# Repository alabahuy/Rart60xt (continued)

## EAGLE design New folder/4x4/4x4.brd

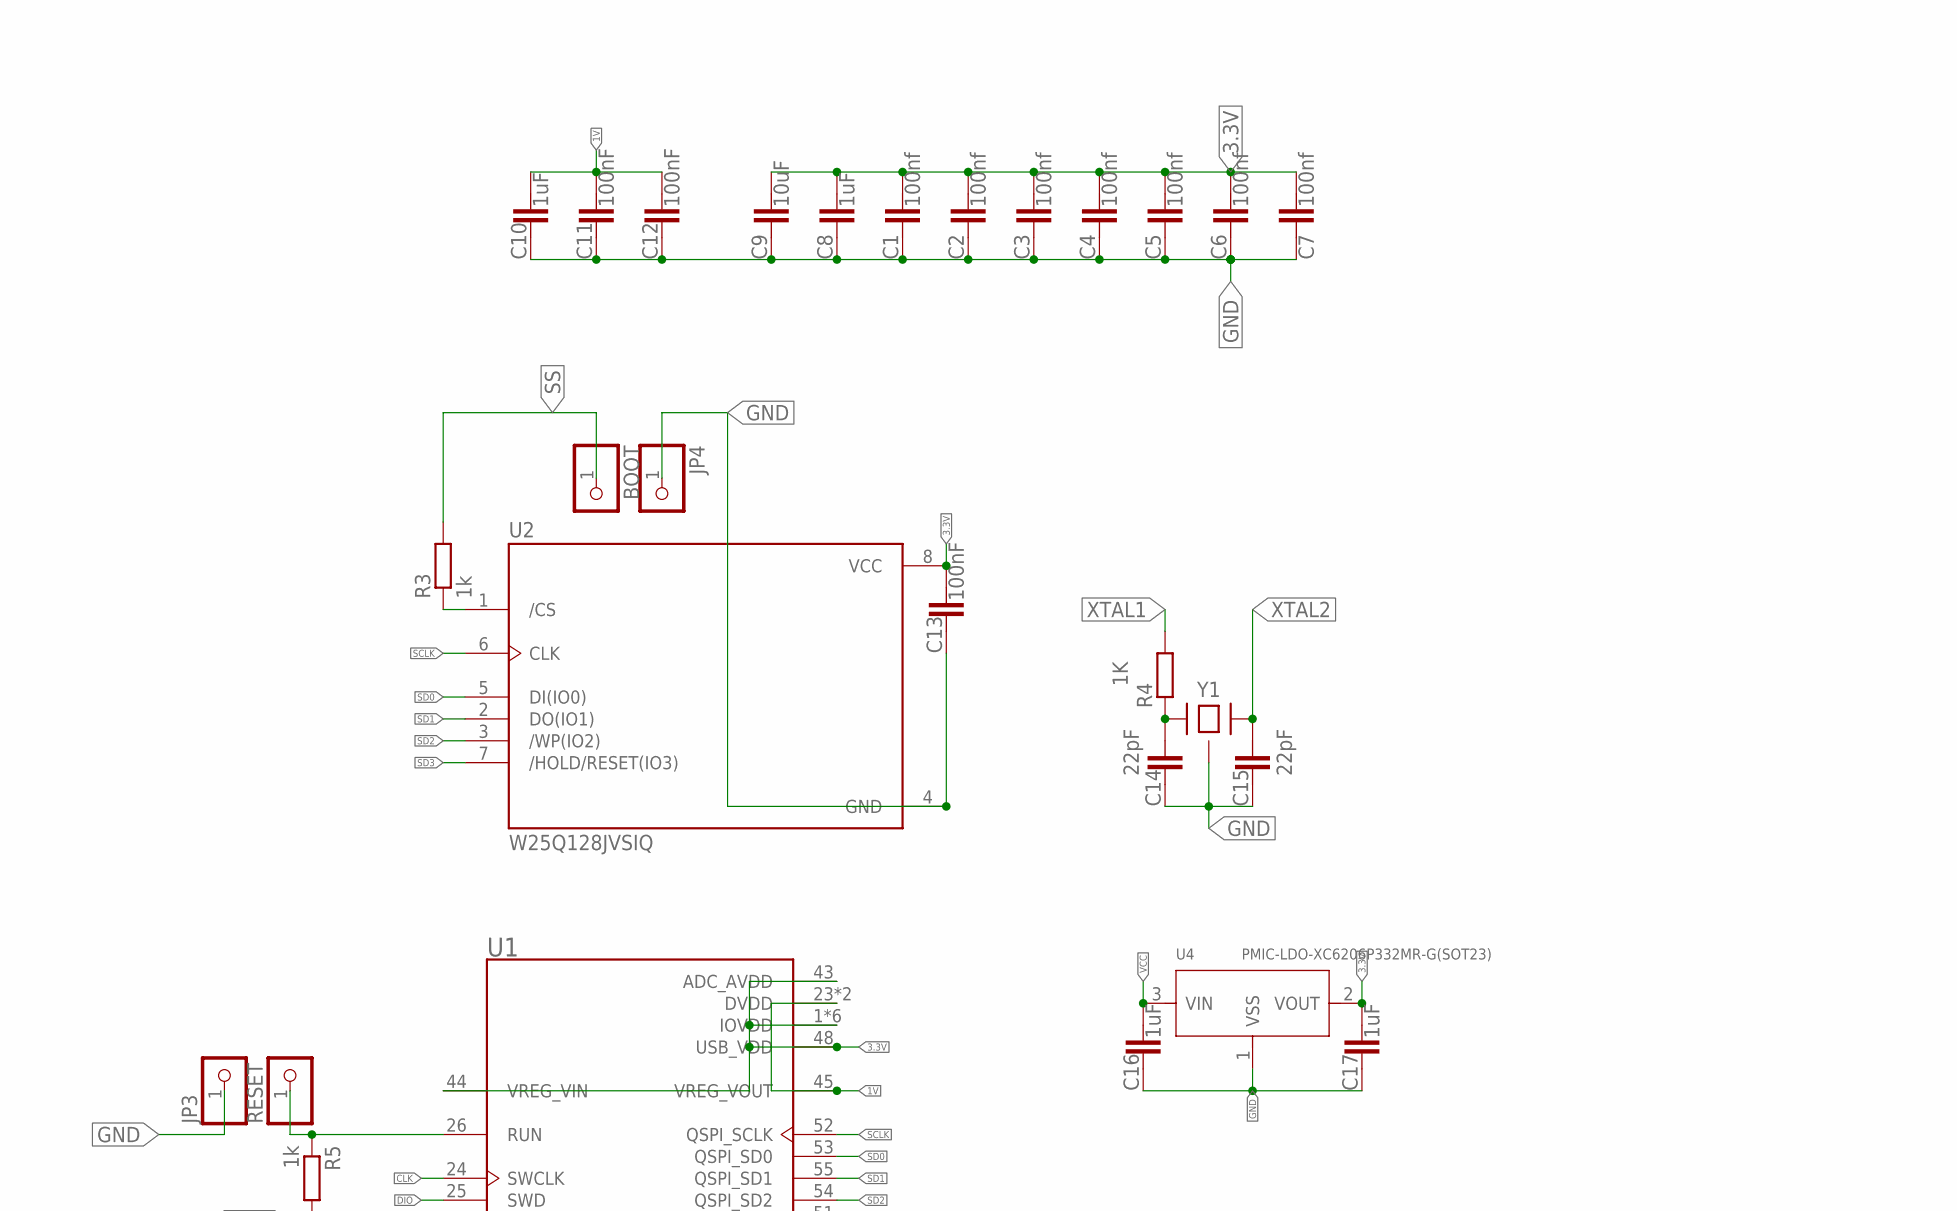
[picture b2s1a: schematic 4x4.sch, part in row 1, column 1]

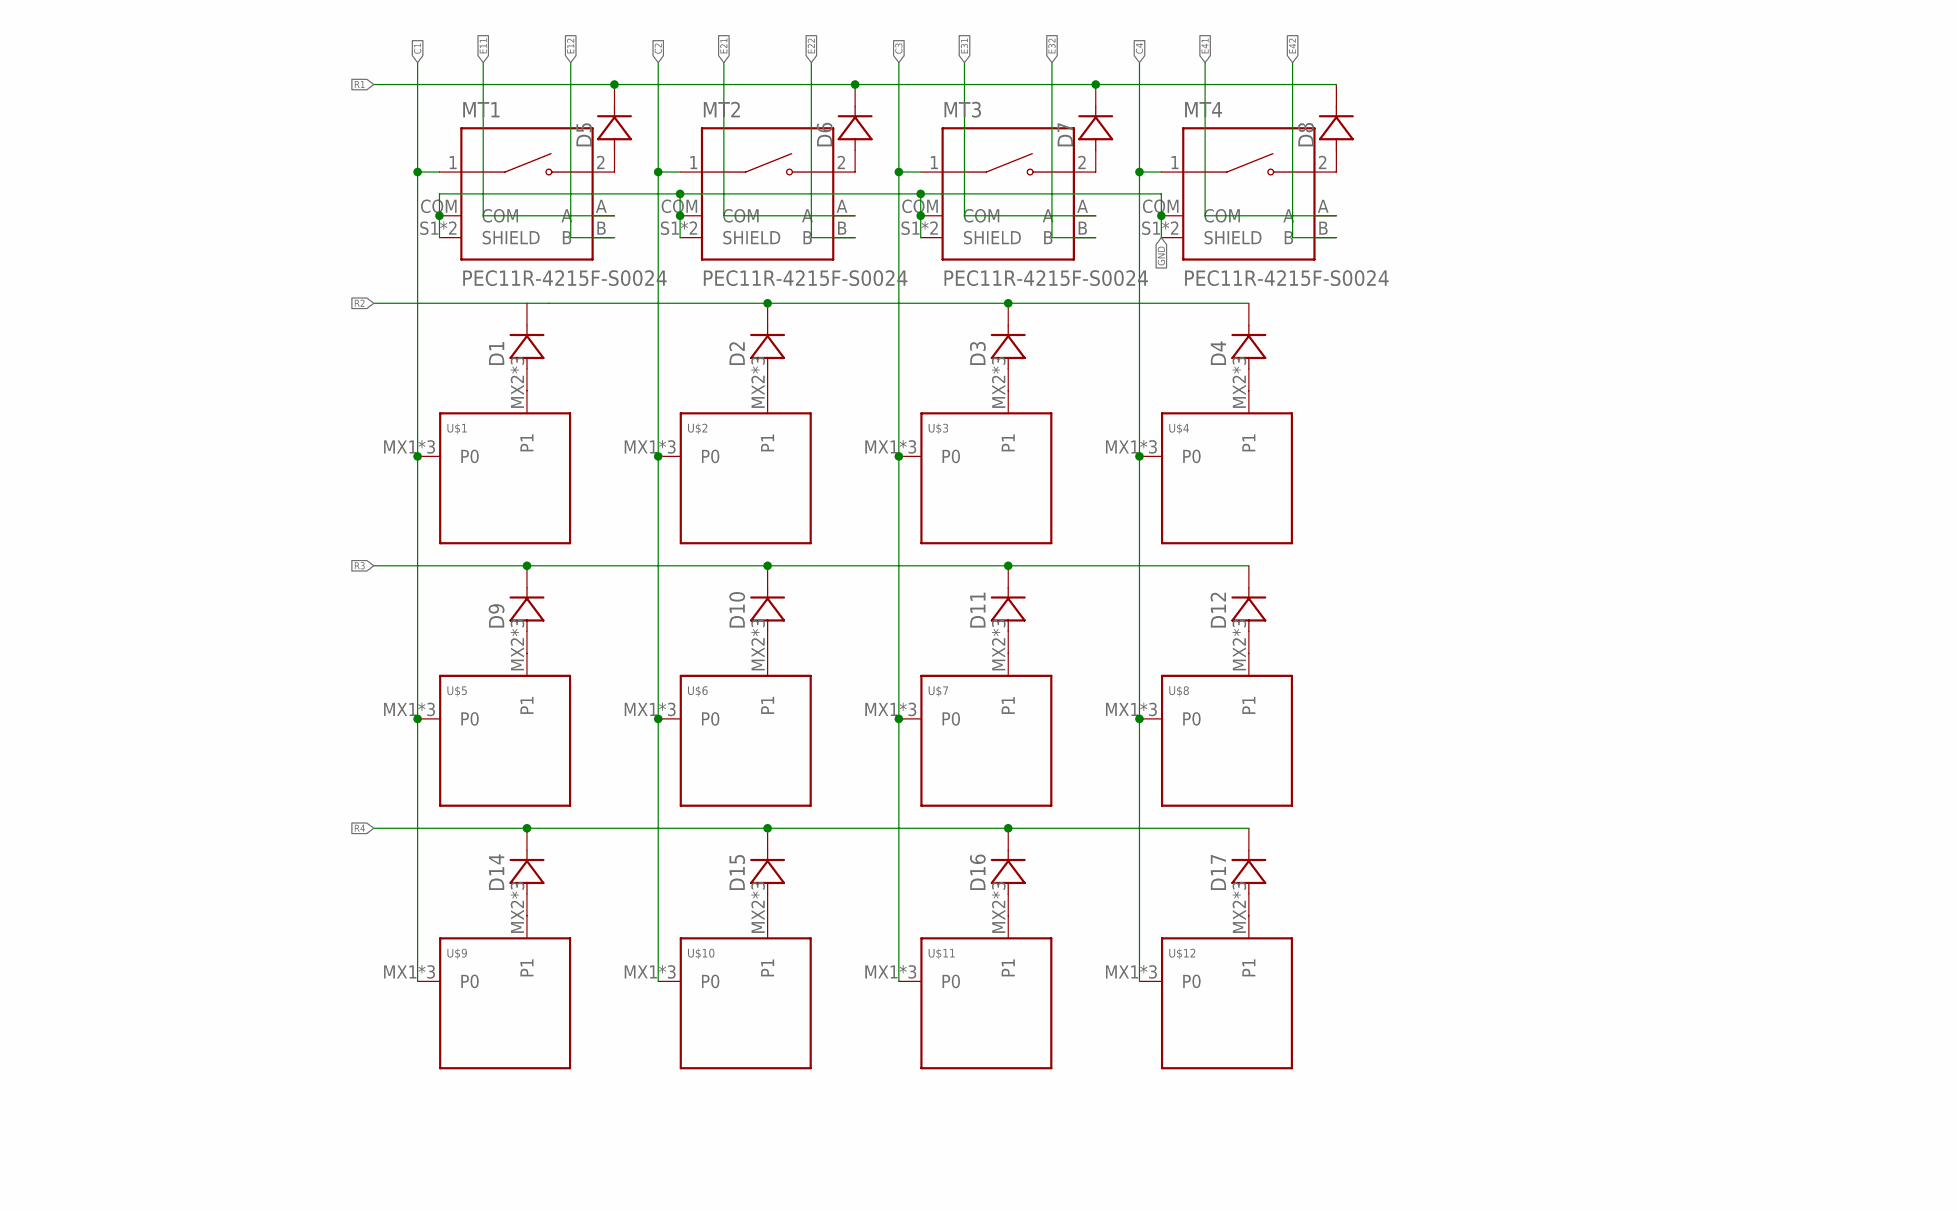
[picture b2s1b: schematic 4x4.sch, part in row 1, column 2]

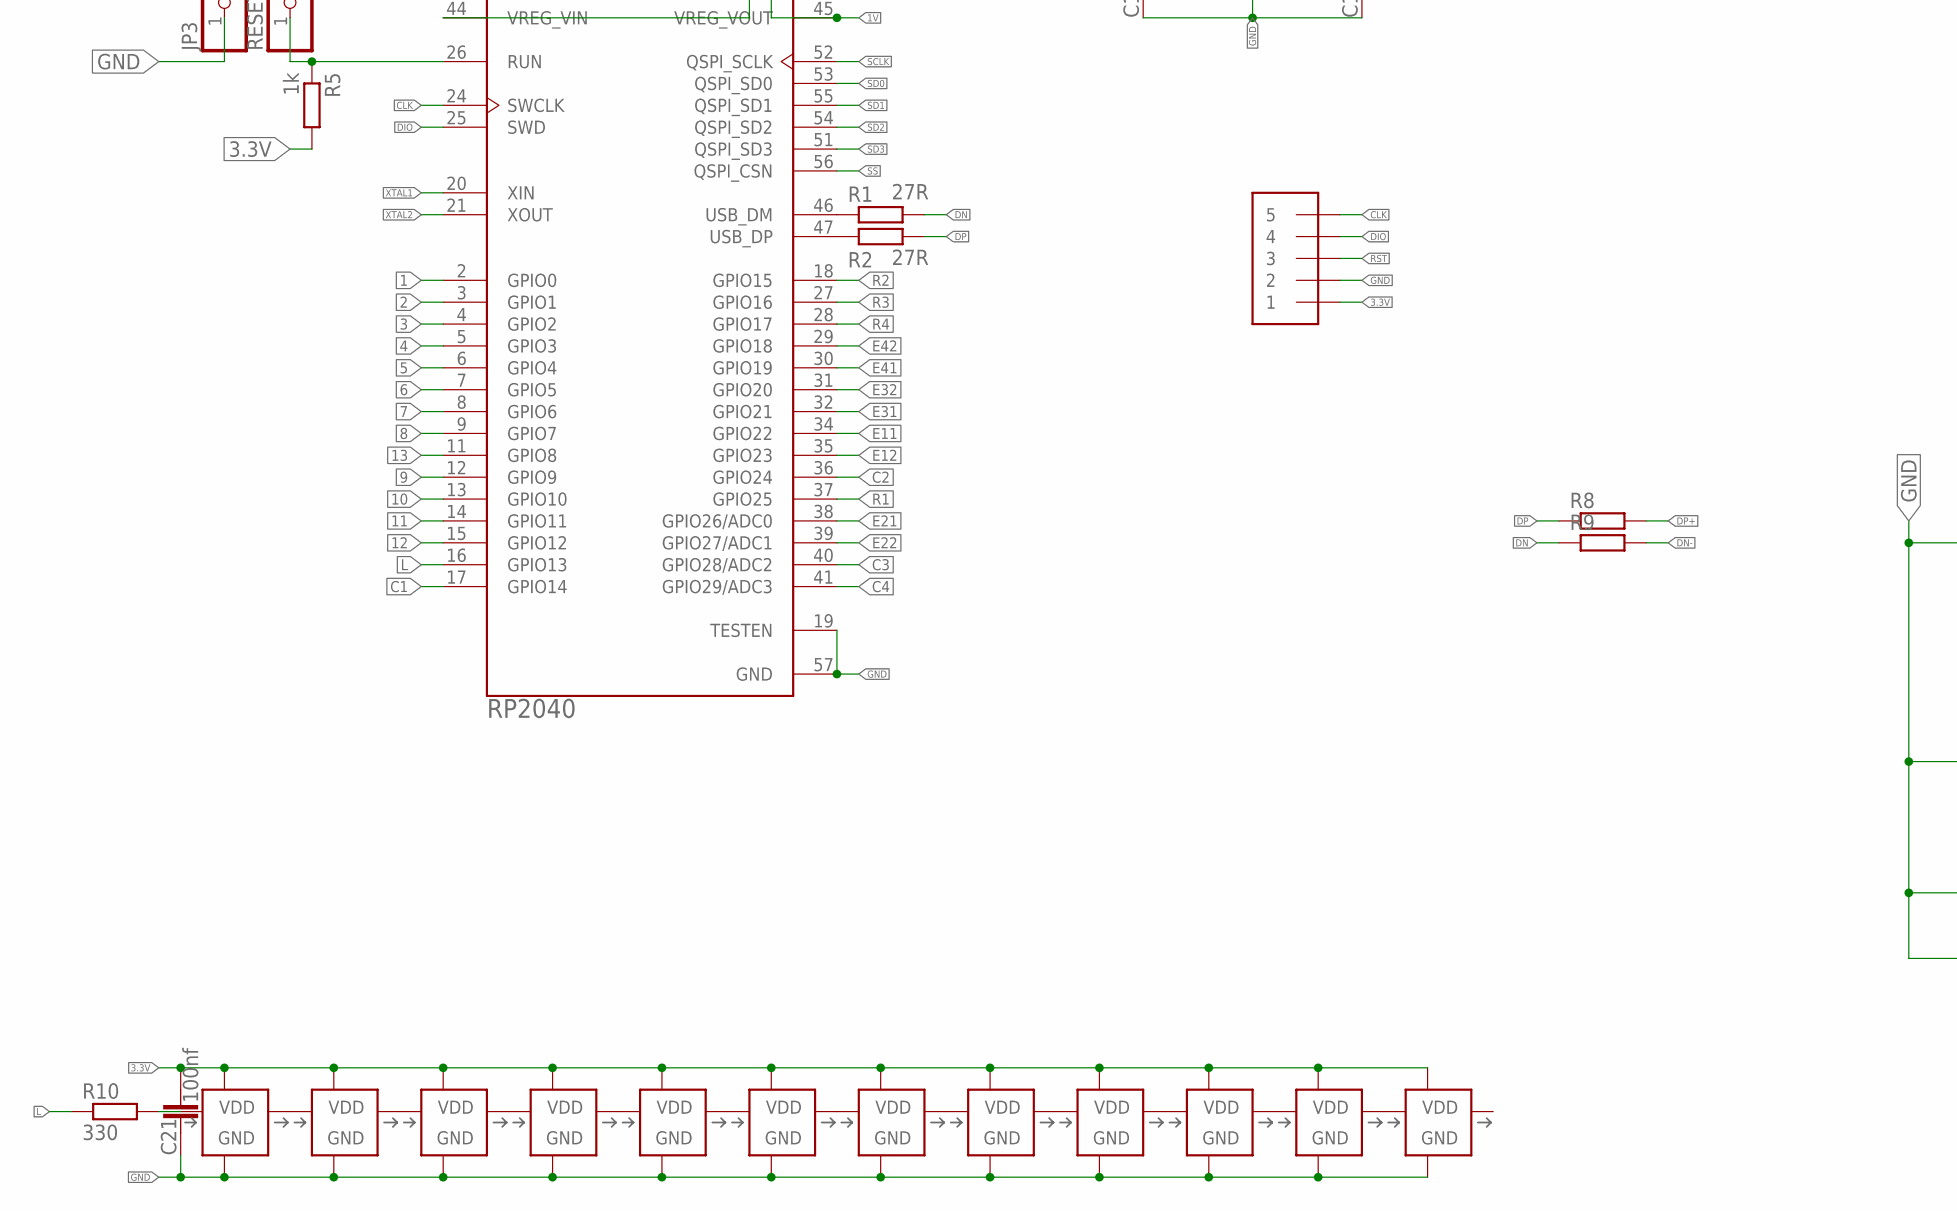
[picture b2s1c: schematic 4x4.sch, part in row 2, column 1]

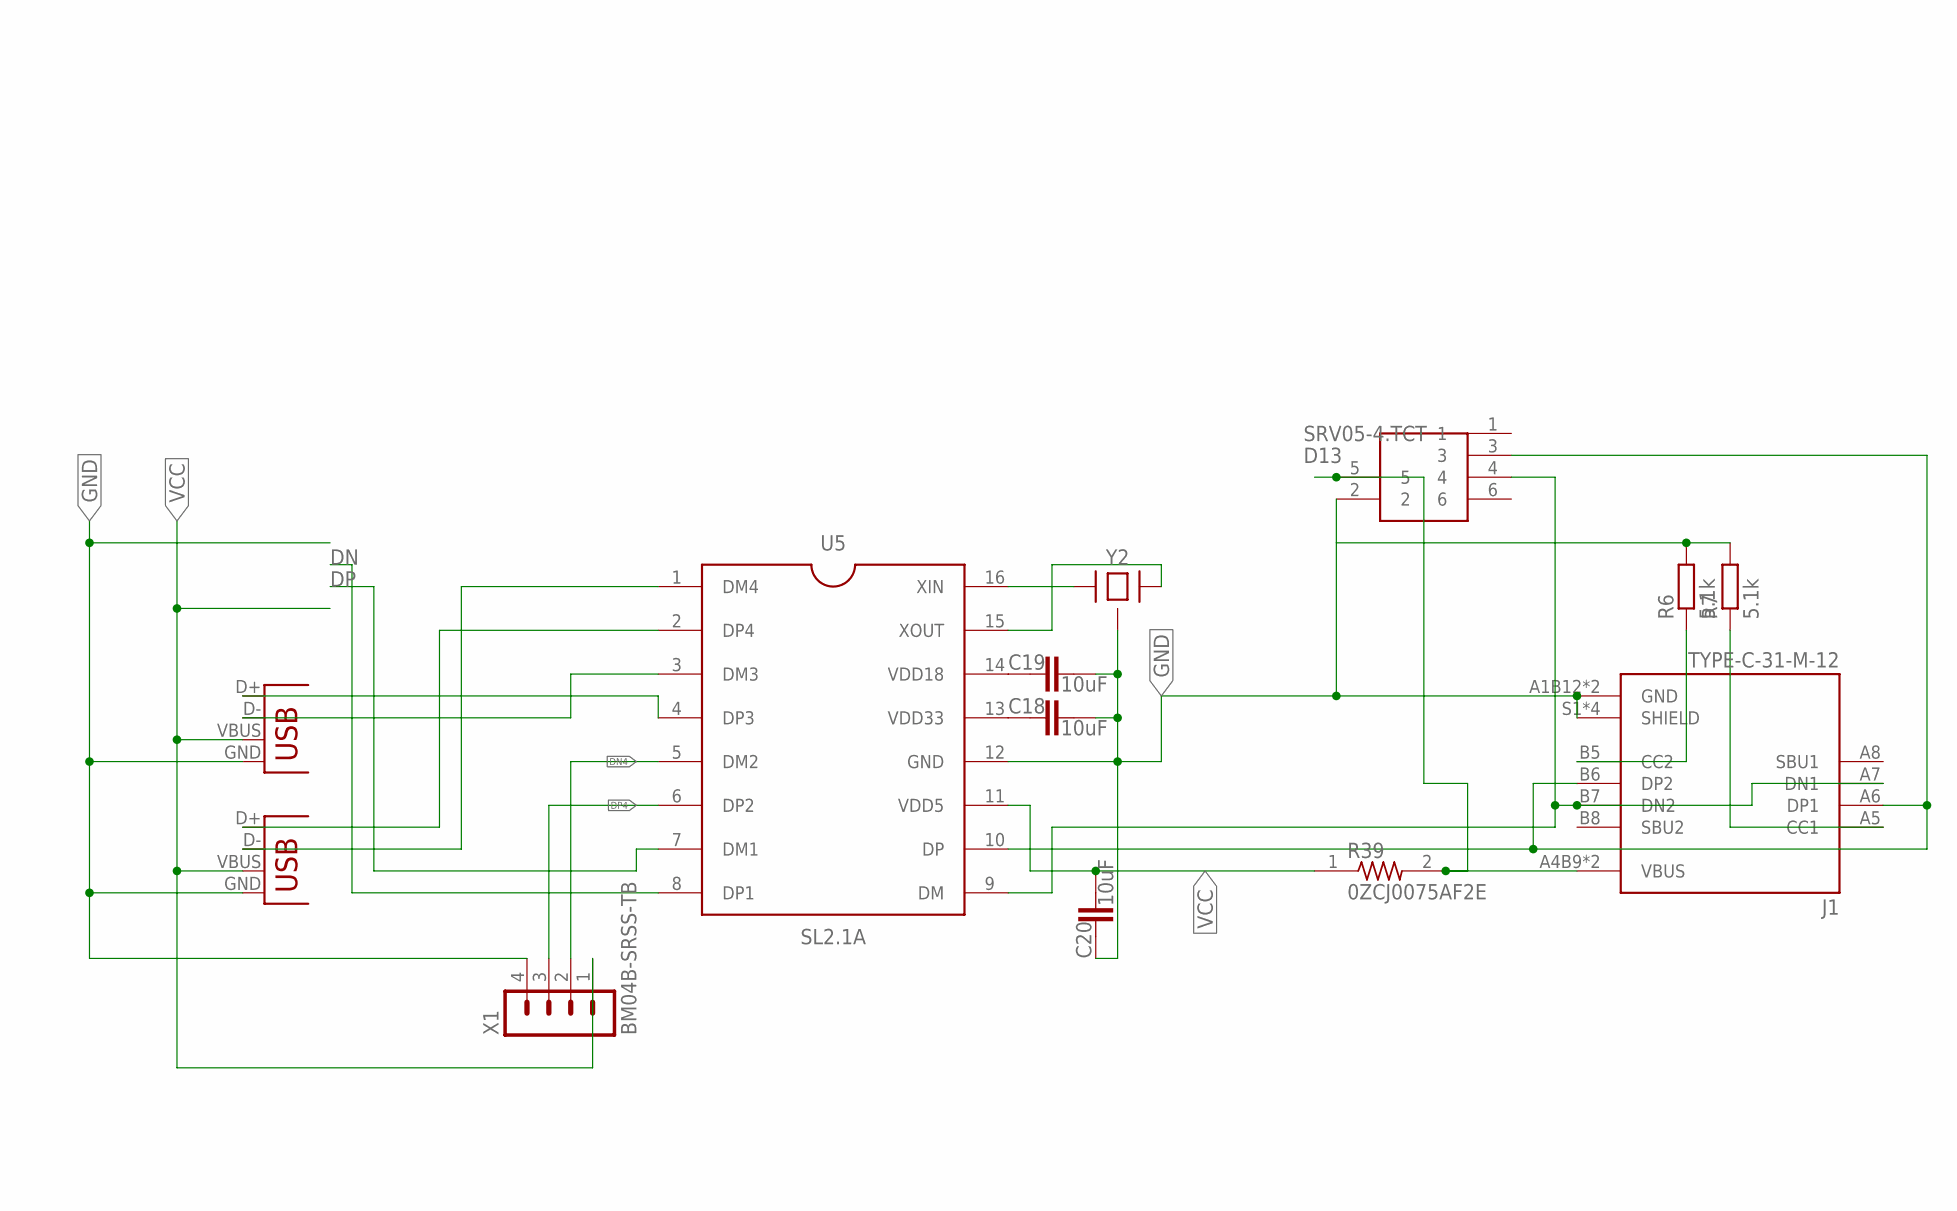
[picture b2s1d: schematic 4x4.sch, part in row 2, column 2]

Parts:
BOOT: PINHD-1X1; 1X01
C1, C2, C3, C4, C5, C6, C7, C21: 100nf; C0603
C8, C10, C16, C17: 1uF; C0603
C9, C18, C19, C20: 10uF; C0603
C11, C12, C13: 100nF; C0603
C14, C15: 22pF; C0603
D1, D2, D3, D4, D5, D6, D7, D8, D9, D10, D11, D12, D14, D15, D16, D17: DIODE-SOD-123; SOD-123
D13: SRV05-4.TCT; SOT95P280X145-6N
J1: TYPE-C-31-M-12; HRO_TYPE-C-31-M-12
J2: 1X5; 1X05-3.5MM
JP3, JP4: PINHD-1X1CB; 1X01-CLEANBIG
MT1, MT2, MT3, MT4: PEC11R-4215F-S0024; XDCR_PEC11R-4215F-S0024
R1, R2: 27R; R0603
R3, R5: 1k; R0603
R4: 1K; R0603
R6, R7: 5.1k; R0603
R8, R9: RESISTOR-0405; R0402
R10: 330; R0603
R39: 0ZCJ0075AF2E; RESC3216X125N
RESET: PINHD-1X1; 1X01
U1: RP2040; QFN40P700X700X90-57N
U2: W25Q128JVSIQ; SOIC127P790X216-8N
U4: PMIC-LDO-XC6206P332MR-G(SOT23); SOT-23
U5: SL2.1A; SO16
U$1, U$2, U$3, U$4, U$5, U$6, U$7, U$8, U$9, U$10, U$11, U$12: KEYSWITCH-PLAIN-MXHSPCB-1U; MXHSPCB-1U
U$13, U$14, U$15, U$16, U$17, U$18, U$19, U$20, U$21, U$22, U$23, U$24: SK6812MINI; LED-3535
X1: BM04B-SRSS-TB
X4, X5: USB-A-H
Y1, Y2: CRYSTAL-4PIN-3.2X2.5; CRYSTAL-3.2X2.5

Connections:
1: U1.2 (GPIO0)
1V: C10.2, C11.2, C12.2, U1.23 (DVDD), U1.45 (VREG_VOUT), U1.50 (DVDD)
2: U1.3 (GPIO1)
3: U1.4 (GPIO2)
3.3V: C1.2, C2.2, C3.2, C4.2, C5.2, C6.2, C7.2, C8.2, C9.2, C13.2, C17.2, C21.2, J2.1, R5.2, U1.1 (IOVDD), U1.10 (IOVDD), U1.22 (IOVDD), U1.33 (IOVDD), U1.42 (IOVDD), U1.43 (ADC_AVDD), U1.44 (VREG_VIN), U1.48 (USB_VDD), U1.49 (IOVDD), U2.8 (VCC), U4.2 (VOUT), U$13.4 (VDD), U$14.4 (VDD), U$15.4 (VDD), U$16.4 (VDD), U$17.4 (VDD), U$18.4 (VDD), U$19.4 (VDD), U$20.4 (VDD), U$21.4 (VDD), U$22.4 (VDD), U$23.4 (VDD), U$24.4 (VDD)
4: U1.5 (GPIO3)
5: U1.6 (GPIO4)
6: U1.7 (GPIO5)
7: U1.8 (GPIO6)
8: U1.9 (GPIO7)
9: U1.12 (GPIO9)
10: U1.13 (GPIO10)
11: U1.14 (GPIO11)
12: U1.15 (GPIO12)
13: U1.11 (GPIO8)
C1: MT1.1, U1.17 (GPIO14), U$1.MX1 (P0), U$1.P$1 (P0), U$1.P$2 (P0), U$5.MX1 (P0), U$5.P$1 (P0), U$5.P$2 (P0), U$9.MX1 (P0), U$9.P$1 (P0), U$9.P$2 (P0)
C2: MT2.1, U1.36 (GPIO24), U$2.MX1 (P0), U$2.P$1 (P0), U$2.P$2 (P0), U$6.MX1 (P0), U$6.P$1 (P0), U$6.P$2 (P0), U$10.MX1 (P0), U$10.P$1 (P0), U$10.P$2 (P0)
C3: MT3.1, U1.40 (GPIO28/ADC2), U$3.MX1 (P0), U$3.P$1 (P0), U$3.P$2 (P0), U$7.MX1 (P0), U$7.P$1 (P0), U$7.P$2 (P0), U$11.MX1 (P0), U$11.P$1 (P0), U$11.P$2 (P0)
C4: MT4.1, U1.41 (GPIO29/ADC3), U$4.MX1 (P0), U$4.P$1 (P0), U$4.P$2 (P0), U$8.MX1 (P0), U$8.P$1 (P0), U$8.P$2 (P0), U$12.MX1 (P0), U$12.P$1 (P0), U$12.P$2 (P0)
CLK: J2.5, U1.24 (SWCLK)
DIO: J2.4, U1.25 (SWD)
DN: R1.2, R9.1, U5.8 (DP1)
DN4: U5.5 (DM2), X1.2
DN-: D13.4, J1.A7 (DN1), J1.B7 (DN2), R9.2, U5.9 (DM)
DP: R2.2, R8.1, U5.7 (DM1)
DP4: U5.6 (DP2), X1.3
DP+: D13.3, J1.A6 (DP1), J1.B6 (DP2), R8.2, U5.10 (DP)
E11: MT1.A, U1.34 (GPIO22)
E12: MT1.B, U1.35 (GPIO23)
E21: MT2.A, U1.38 (GPIO26/ADC0)
E22: MT2.B, U1.39 (GPIO27/ADC1)
E31: MT3.A, U1.32 (GPIO21)
E32: MT3.B, U1.31 (GPIO20)
E41: MT4.A, U1.30 (GPIO19)
E42: MT4.B, U1.29 (GPIO18)
GND: C1.1, C2.1, C3.1, C4.1, C5.1, C6.1, C7.1, C8.1, C9.1, C10.1, C11.1, C12.1, C13.1, C14.1, C15.1, C16.1, C17.1, C18.2, C19.2, C20.1, C21.1, D13.2, J1.A1B12 (GND), J1.B1A12 (GND), J1.S1 (SHIELD), J1.S2 (SHIELD), J1.S3 (SHIELD), J1.S4 (SHIELD), J2.2, JP3.1, JP4.1, MT1.COM, MT1.S1 (SHIELD), MT1.S2 (SHIELD), MT2.COM, MT2.S1 (SHIELD), MT2.S2 (SHIELD), MT3.COM, MT3.S1 (SHIELD), MT3.S2 (SHIELD), MT4.COM, MT4.S1 (SHIELD), MT4.S2 (SHIELD), R6.2, R7.2, U1.19 (TESTEN), U1.57 (GND), U2.4 (GND), U4.1 (VSS), U5.12 (GND), U$13.2 (GND), U$14.2 (GND), U$15.2 (GND), U$16.2 (GND), U$17.2 (GND), U$18.2 (GND), U$19.2 (GND), U$20.2 (GND), U$21.2 (GND), U$22.2 (GND), U$23.2 (GND), U$24.2 (GND), X1.4, X4.GND, X5.GND, Y1.2 (GND), Y1.4 (GND), Y2.2 (GND), Y2.4 (GND)
L: R10.1, U1.16 (GPIO13)
unnamed: D13.5, J1.A4B9 (VBUS), J1.B4A9 (VBUS), R39.2
unnamed: U$13.1 (DI), U$19.3 (DO)
unnamed: U$13.3 (DO), U$14.1 (DI)
unnamed: U$14.3 (DO), U$15.1 (DI)
unnamed: U$15.3 (DO), U$16.1 (DI)
unnamed: U$16.3 (DO), U$20.1 (DI)
unnamed: R1.1, U1.46 (USB_DM)
unnamed: R2.1, U1.47 (USB_DP)
unnamed: C14.2, R4.1, Y1.1
unnamed: R3.1, U2.1 (/CS)
unnamed: D1.A, U$1.MX2 (P1), U$1.P$3 (P1), U$1.P$4 (P1)
unnamed: D2.A, U$2.MX2 (P1), U$2.P$3 (P1), U$2.P$4 (P1)
unnamed: C18.1, U5.13 (VDD33)
unnamed: C19.1, U5.14 (VDD18)
unnamed: U5.16 (XIN), Y2.1
unnamed: U5.15 (XOUT), Y2.3 (2)
unnamed: U5.2 (DP4), X5.D+
unnamed: U5.1 (DM4), X5.D-
unnamed: U$20.3 (DO), U$21.1 (DI)
unnamed: U$21.3 (DO), U$22.1 (DI)
unnamed: U5.3 (DM3), X4.D-
unnamed: U5.4 (DP3), X4.D+
unnamed: U$22.3 (DO), U$23.1 (DI)
unnamed: U$23.3 (DO), U$24.1 (DI)
unnamed: D3.A, U$3.MX2 (P1), U$3.P$3 (P1), U$3.P$4 (P1)
unnamed: D4.A, U$4.MX2 (P1), U$4.P$3 (P1), U$4.P$4 (P1)
unnamed: D5.A, MT1.2
unnamed: D6.A, MT2.2
unnamed: D7.A, MT3.2
unnamed: D8.A, MT4.2
unnamed: D9.A, U$5.MX2 (P1), U$5.P$3 (P1), U$5.P$4 (P1)
unnamed: D10.A, U$6.MX2 (P1), U$6.P$3 (P1), U$6.P$4 (P1)
unnamed: D11.A, U$7.MX2 (P1), U$7.P$3 (P1), U$7.P$4 (P1)
unnamed: D12.A, U$8.MX2 (P1), U$8.P$3 (P1), U$8.P$4 (P1)
unnamed: D14.A, U$9.MX2 (P1), U$9.P$3 (P1), U$9.P$4 (P1)
unnamed: D15.A, U$10.MX2 (P1), U$10.P$3 (P1), U$10.P$4 (P1)
unnamed: D16.A, U$11.MX2 (P1), U$11.P$3 (P1), U$11.P$4 (P1)
unnamed: D17.A, U$12.MX2 (P1), U$12.P$3 (P1), U$12.P$4 (P1)
unnamed: U$17.3 (DO), U$18.1 (DI)
unnamed: U$18.3 (DO), U$19.1 (DI)
unnamed: J1.B5 (CC2), R6.1
unnamed: J1.A5 (CC1), R7.1
R1: D5.C, D6.C, D7.C, D8.C, U1.37 (GPIO25)
R2: D1.C, D2.C, D3.C, D4.C, U1.18 (GPIO15)
R3: D9.C, D10.C, D11.C, D12.C, U1.27 (GPIO16)
R4: D14.C, D15.C, D16.C, D17.C, U1.28 (GPIO17)
RGB: R10.2, U$17.1 (DI)
RST: J2.3, R5.1, RESET.1, U1.26 (RUN)
SCLK: U1.52 (QSPI_SCLK), U2.6 (CLK)
SD0: U1.53 (QSPI_SD0), U2.5 (DI(IO0))
SD1: U1.55 (QSPI_SD1), U2.2 (DO(IO1))
SD2: U1.54 (QSPI_SD2), U2.3 (/WP(IO2))
SD3: U1.51 (QSPI_SD3), U2.7 (/HOLD/RESET(IO3))
SS: BOOT.1, R3.2, U1.56 (QSPI_CSN)
VCC: C16.2, C20.2, R39.1, U4.3 (VIN), U5.11 (VDD5), X1.1, X4.VBUS, X5.VBUS
XTAL1: R4.2, U1.20 (XIN)
XTAL2: C15.2, U1.21 (XOUT), Y1.3 (2)

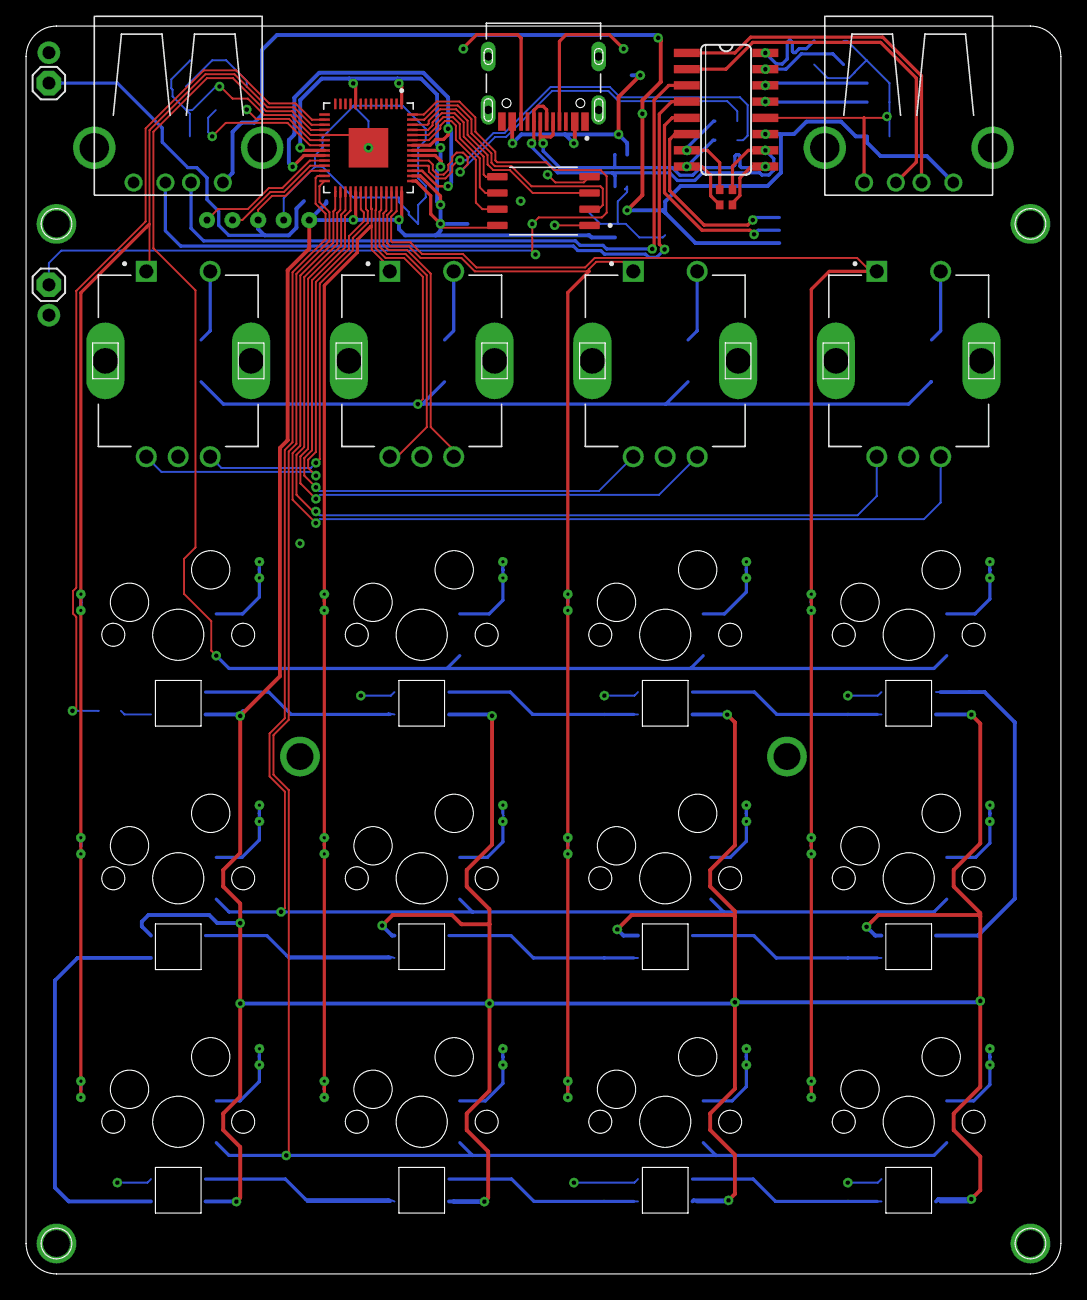
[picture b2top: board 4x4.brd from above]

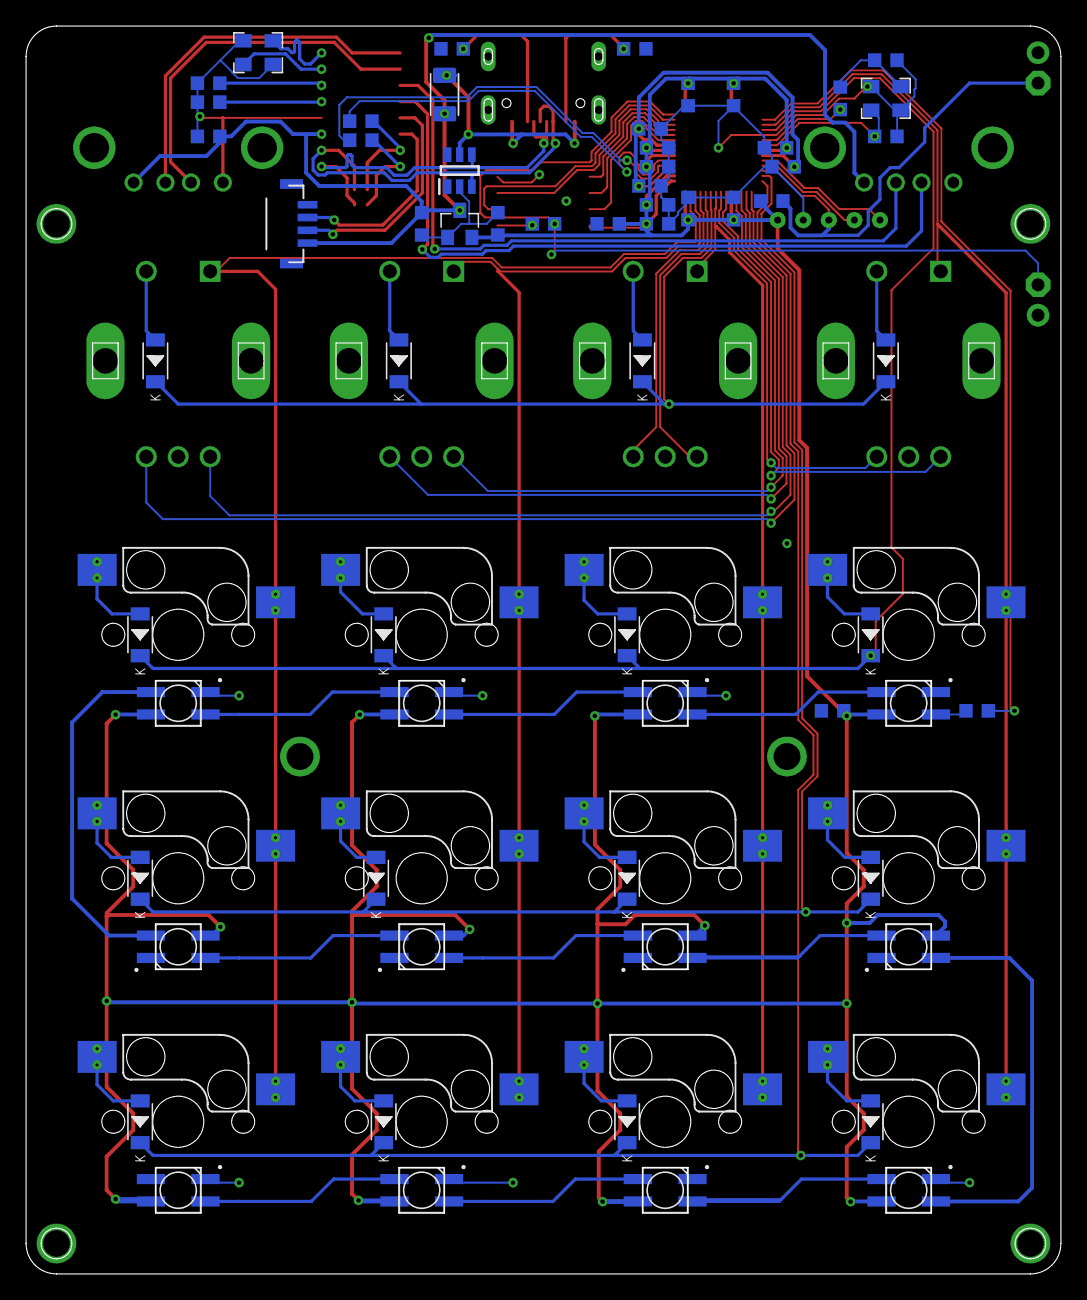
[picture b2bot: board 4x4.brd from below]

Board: 2 copper layers, 81.0 x 97.6 mm, 92 parts (75 on the bottom side), 81 nets.
